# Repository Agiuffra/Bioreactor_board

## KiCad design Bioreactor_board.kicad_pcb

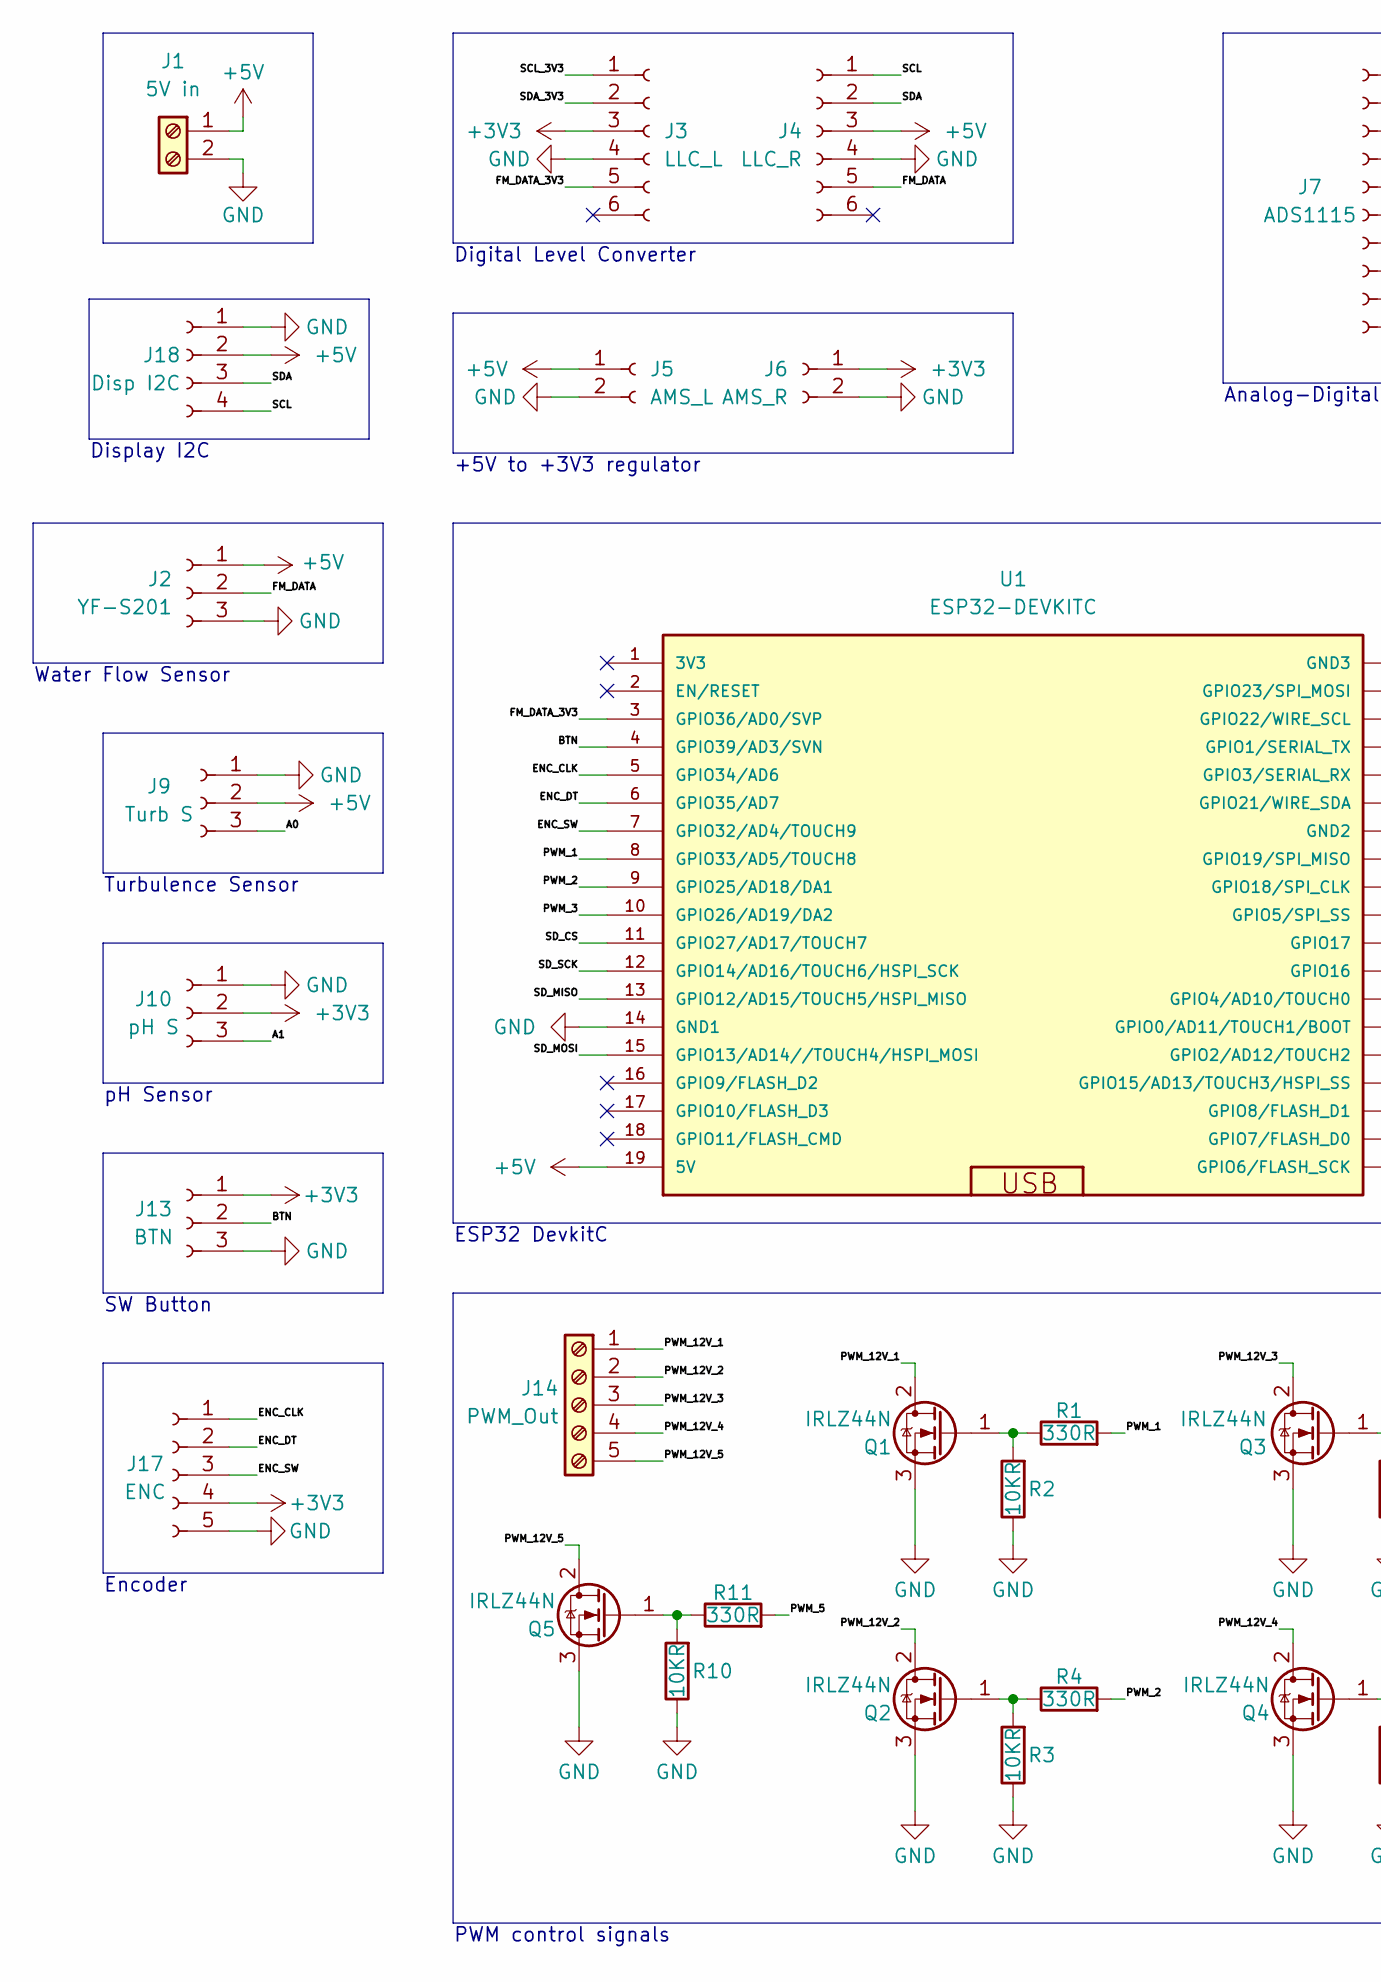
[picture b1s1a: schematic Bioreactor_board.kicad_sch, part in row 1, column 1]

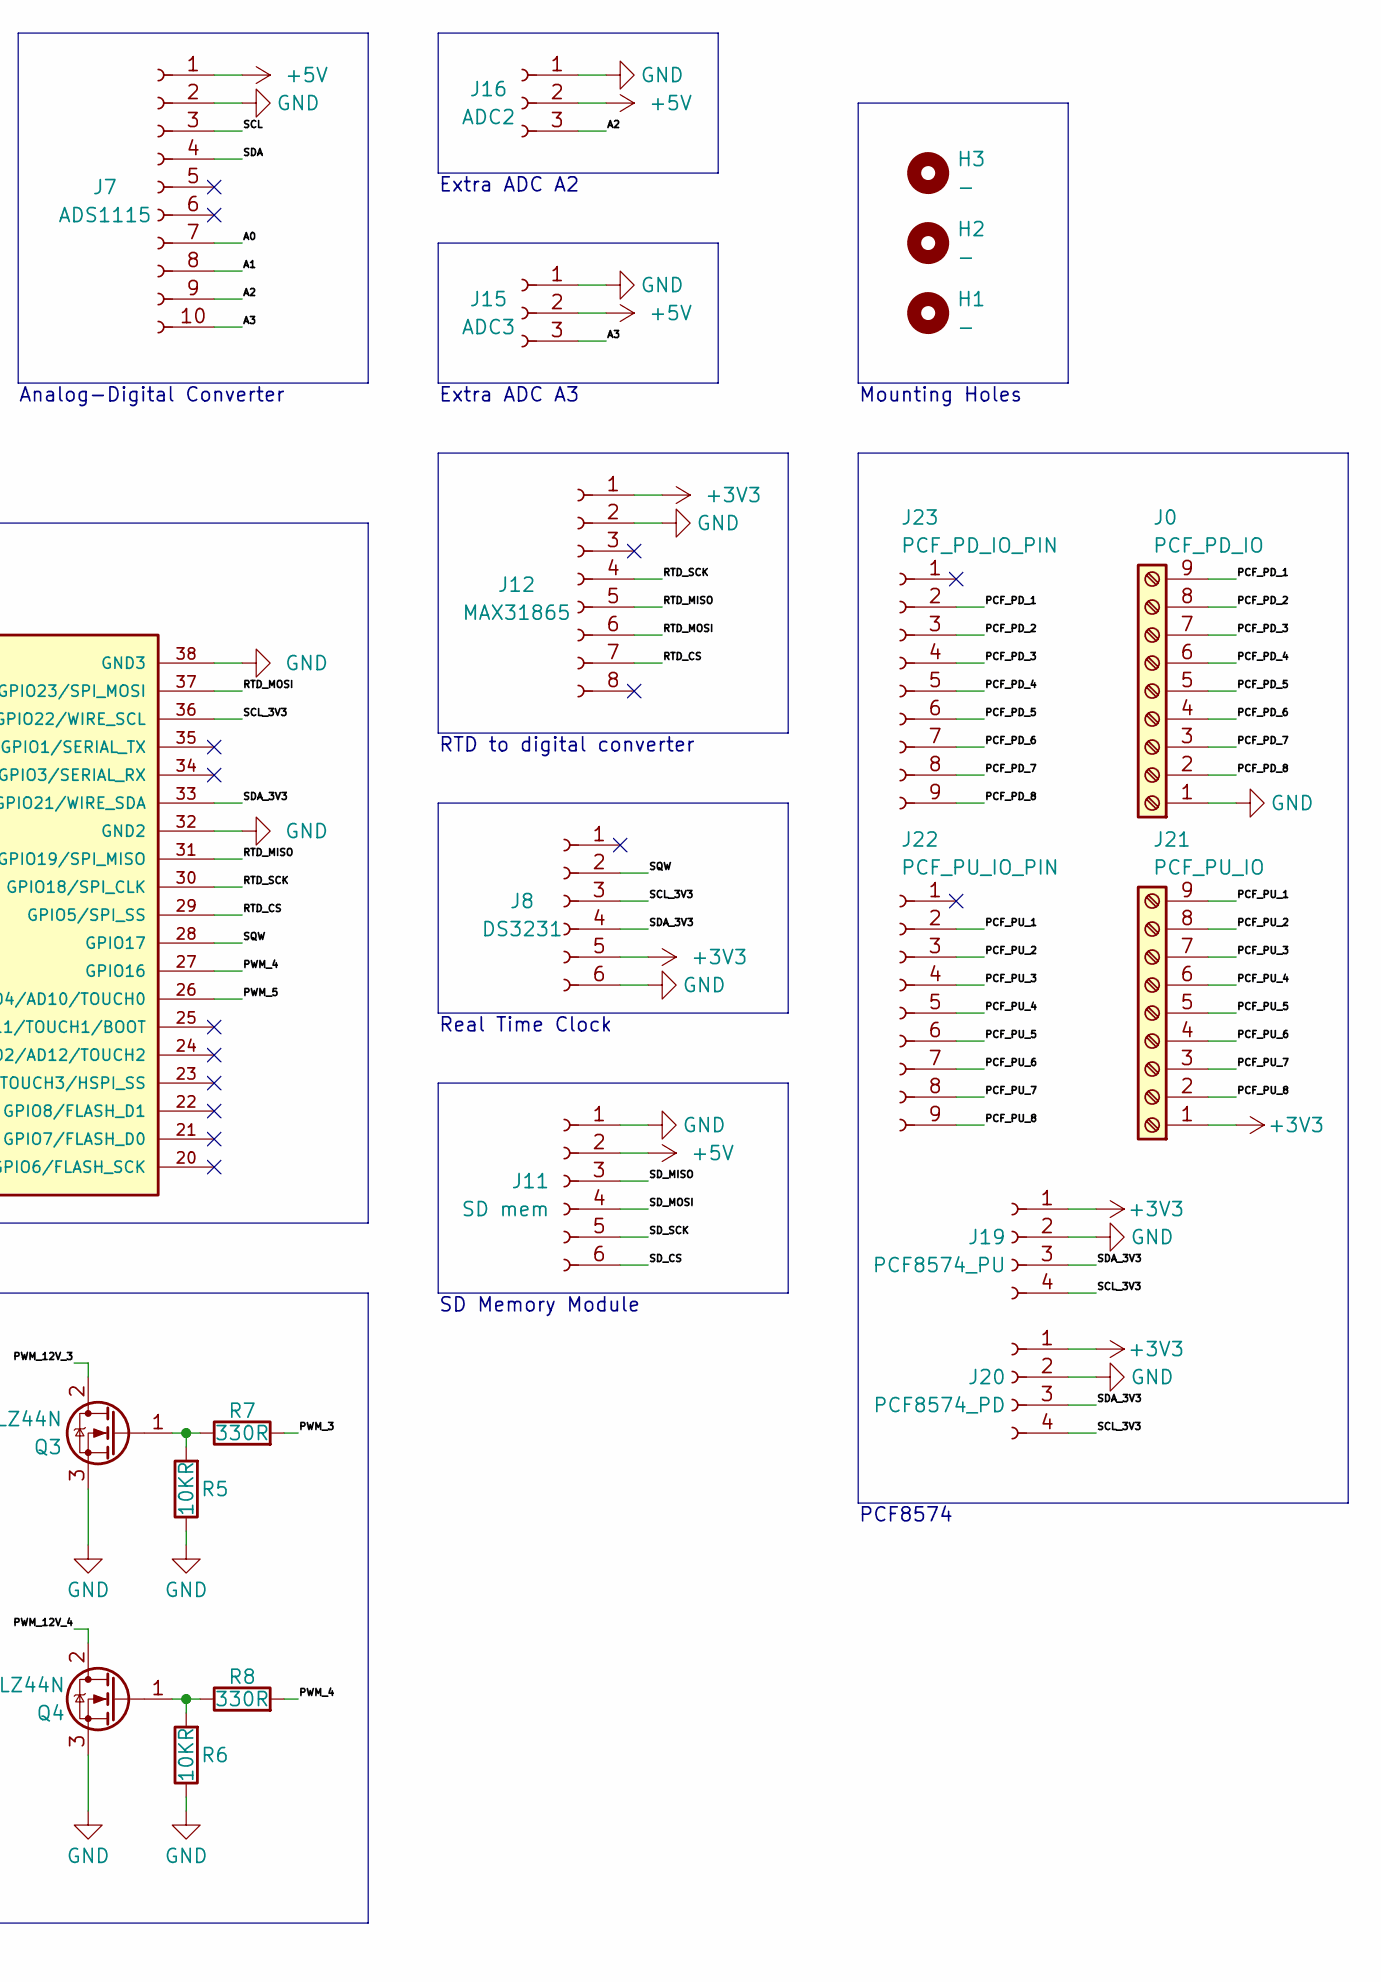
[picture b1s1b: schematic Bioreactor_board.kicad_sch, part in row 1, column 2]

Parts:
H1, H2, H3: -; MountingHole_3.2mm_M3
J0: PCF_PD_IO; TerminalBlock_RND_205-00239_1x09_P5.08mm_Horizontal
J1: 5V in; TerminalBlock_bornier-2_P5.08mm
J2: YF-S201; Molex_KK-254_AE-6410-03A_1x03_P2.54mm_Vertical
J3: LLC_L; PinSocket_1x06_P2.54mm_Vertical
J4: LLC_R; PinSocket_1x06_P2.54mm_Vertical
J5: AMS_L; PinSocket_1x02_P2.54mm_Vertical
J6: AMS_R; PinSocket_1x02_P2.54mm_Vertical
J7: ADS1115; PinHeader_1x10_P2.54mm_Vertical
J8: DS3231; PinSocket_1x06_P2.54mm_Vertical
J9: Turb S; Molex_KK-254_AE-6410-03A_1x03_P2.54mm_Vertical
J10: pH S; Molex_KK-254_AE-6410-03A_1x03_P2.54mm_Vertical
J11: SD mem; PinSocket_1x06_P2.54mm_Vertical
J12: MAX31865; PinSocket_1x08_P2.54mm_Vertical
J13: BTN; PinSocket_1x03_P2.54mm_Vertical
J14: PWM_Out; TerminalBlock_bornier-5_P5.08mm
J15: ADC3; Molex_KK-254_AE-6410-03A_1x03_P2.54mm_Vertical
J16: ADC2; Molex_KK-254_AE-6410-03A_1x03_P2.54mm_Vertical
J17: ENC; Molex_KK-254_AE-6410-05A_1x05_P2.54mm_Vertical
J18: Disp I2C; Molex_KK-254_AE-6410-04A_1x04_P2.54mm_Vertical
J19: PCF8574_PU; PinSocket_1x04_P2.54mm_Vertical
J20: PCF8574_PD; PinSocket_1x04_P2.54mm_Vertical
J21: PCF_PU_IO; TerminalBlock_RND_205-00239_1x09_P5.08mm_Horizontal
J22: PCF_PU_IO_PIN; PinSocket_1x09_P2.54mm_Vertical
J23: PCF_PD_IO_PIN; PinSocket_1x09_P2.54mm_Vertical
Q1, Q2, Q3, Q4, Q5: IRLZ44N; TO-220-3_Vertical
R1, R4, R7, R8, R11: 330R; R_Axial_DIN0207_L6.3mm_D2.5mm_P10.16mm_Horizontal
R2, R3, R5, R6, R10: 10KR; R_Axial_DIN0207_L6.3mm_D2.5mm_P10.16mm_Horizontal
U1: ESP32-DEVKITC

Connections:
+3V3: J3.3, J6.1, J8.5, J10.2, J12.1, J13.1, J17.4, J19.1, J20.1, J21.1
+5V: J1.1, J2.1, J4.3, J5.1, J7.1, J9.2, J11.2, J15.2, J16.2, J18.2, U1.19 (5V)
/A0: J7.7, J9.3
/A1: J7.8, J10.3
/A2: J7.9, J16.3
/A3: J7.10, J15.3
/BTN: J13.2, U1.4 (GPIO39/AD3/SVN)
/ENC_CLK: J17.1, U1.5 (GPIO34/AD6)
/ENC_DT: J17.2, U1.6 (GPIO35/AD7)
/ENC_SW: J17.3, U1.7 (GPIO32/AD4/TOUCH9)
/FM_DATA: J2.2, J4.5
/FM_DATA_3V3: J3.5, U1.3 (GPIO36/AD0/SVP)
/PCF_PD_1: J0.9, J23.2
/PCF_PD_2: J0.8, J23.3
/PCF_PD_3: J0.7, J23.4
/PCF_PD_4: J0.6, J23.5
/PCF_PD_5: J0.5, J23.6
/PCF_PD_6: J0.4, J23.7
/PCF_PD_7: J0.3, J23.8
/PCF_PD_8: J0.2, J23.9
/PCF_PU_1: J21.9, J22.2
/PCF_PU_2: J21.8, J22.3
/PCF_PU_3: J21.7, J22.4
/PCF_PU_4: J21.6, J22.5
/PCF_PU_5: J21.5, J22.6
/PCF_PU_6: J21.4, J22.7
/PCF_PU_7: J21.3, J22.8
/PCF_PU_8: J21.2, J22.9
/PWM_1: R1.2, U1.8 (GPIO33/AD5/TOUCH8)
/PWM_2: R4.2, U1.9 (GPIO25/AD18/DA1)
/PWM_3: R7.2, U1.10 (GPIO26/AD19/DA2)
/PWM_4: R8.2, U1.27 (GPIO16)
/PWM_5: R11.2, U1.26 (GPIO4/AD10/TOUCH0)
/PWM_12V_1: J14.1, Q1.2 (D)
/PWM_12V_2: J14.2, Q2.2 (D)
/PWM_12V_3: J14.3, Q3.2 (D)
/PWM_12V_4: J14.4, Q4.2 (D)
/PWM_12V_5: J14.5, Q5.2 (D)
/RTD_CS: J12.7, U1.29 (GPIO5/SPI_SS)
/RTD_MISO: J12.5, U1.31 (GPIO19/SPI_MISO)
/RTD_MOSI: J12.6, U1.37 (GPIO23/SPI_MOSI)
/RTD_SCK: J12.4, U1.30 (GPIO18/SPI_CLK)
/SCL: J4.1, J7.3, J18.4
/SCL_3V3: J3.1, J8.3, J19.4, J20.4, U1.36 (GPIO22/WIRE_SCL)
/SDA: J4.2, J7.4, J18.3
/SDA_3V3: J3.2, J8.4, J19.3, J20.3, U1.33 (GPIO21/WIRE_SDA)
/SD_CS: J11.6, U1.11 (GPIO27/AD17/TOUCH7)
/SD_MISO: J11.3, U1.13 (GPIO12/AD15/TOUCH5/HSPI_MISO)
/SD_MOSI: J11.4, U1.15 (GPIO13/AD14//TOUCH4/HSPI_MOSI)
/SD_SCK: J11.5, U1.12 (GPIO14/AD16/TOUCH6/HSPI_SCK)
/SQW: J8.2, U1.28 (GPIO17)
GND: J0.1, J1.2, J2.3, J3.4, J4.4, J5.2, J6.2, J7.2, J8.6, J9.1, J10.1, J11.1, J12.2, J13.3, J15.1, J16.1, J17.5, J18.1, J19.2, J20.2, Q1.3 (S), Q2.3 (S), Q3.3 (S), Q4.3 (S), Q5.3 (S), R2.1, R3.1, R5.1, R6.1, R10.1, U1.14 (GND1), U1.32 (GND2), U1.38 (GND3)
unnamed: Q1.1 (G), R1.1, R2.2
unnamed: Q2.1 (G), R3.2, R4.1
unnamed: Q3.1 (G), R5.2, R7.1
unnamed: Q4.1 (G), R6.2, R8.1
unnamed: Q5.1 (G), R10.2, R11.1

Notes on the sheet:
Turbulence Sensor
SW Button
PCF8574
PWM control signals
+5V to +3V3 regulator
RTD to digital converter
Mounting Holes
pH Sensor
Analog-Digital Converter
Extra ADC A3
Display I2C
SD Memory Module
Real Time Clock
Encoder
ESP32 DevkitC
Digital Level Converter
Extra ADC A2
Water Flow Sensor

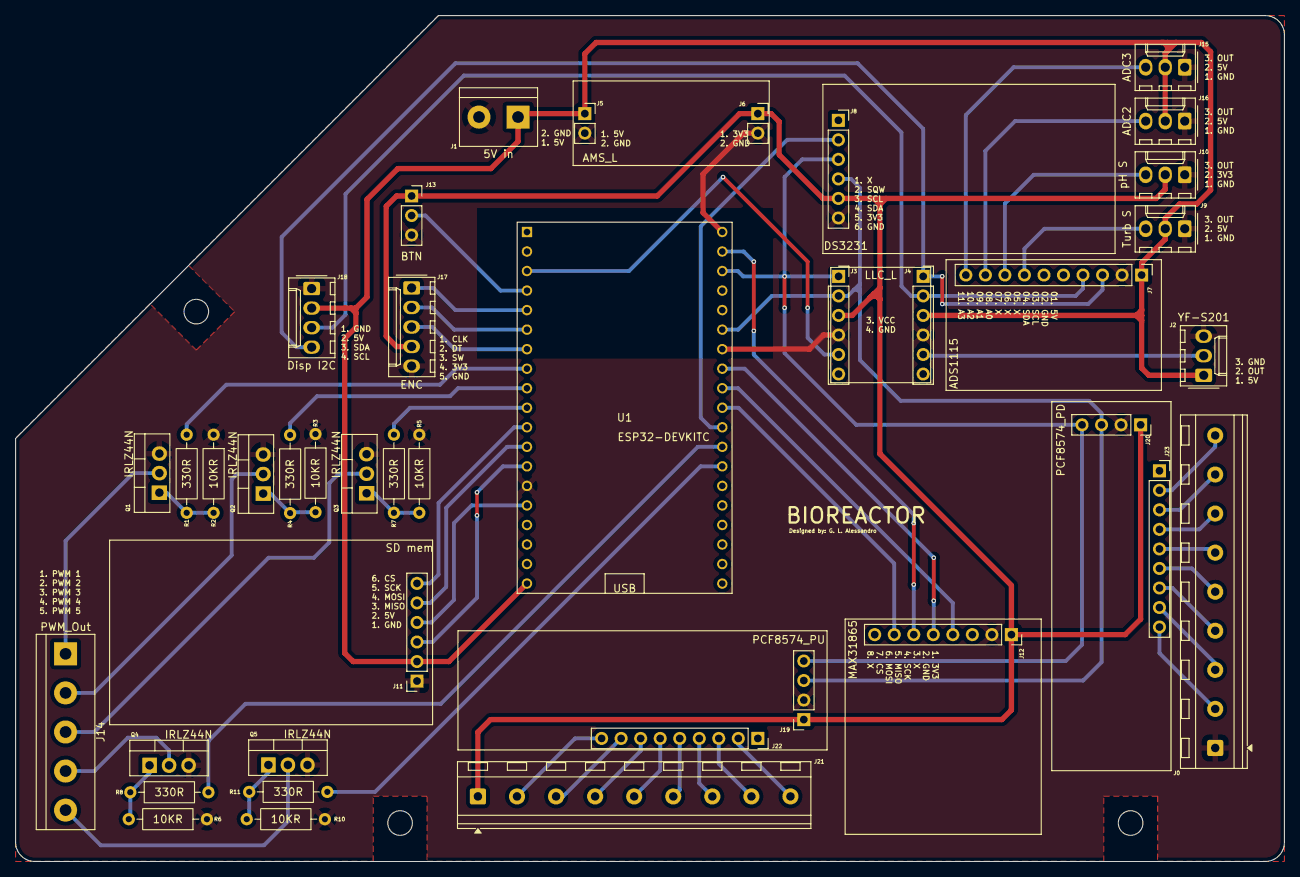
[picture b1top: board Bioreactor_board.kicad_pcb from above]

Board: 2 copper layers, 165.0 x 110.0 mm, 43 parts (0 on the bottom side), 57 nets.

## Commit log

2025-07-18 license and readme added
2025-07-23 Fixed connections and first version of brd
2025-07-24 Second Iteration of brd
2025-07-24 PDF added
